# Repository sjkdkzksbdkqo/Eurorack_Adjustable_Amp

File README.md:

# Eurorack_Adjustable_Amp
2HP TL072-based 1 Channel Non-Inverting Amp with adjustable gain and Offset.

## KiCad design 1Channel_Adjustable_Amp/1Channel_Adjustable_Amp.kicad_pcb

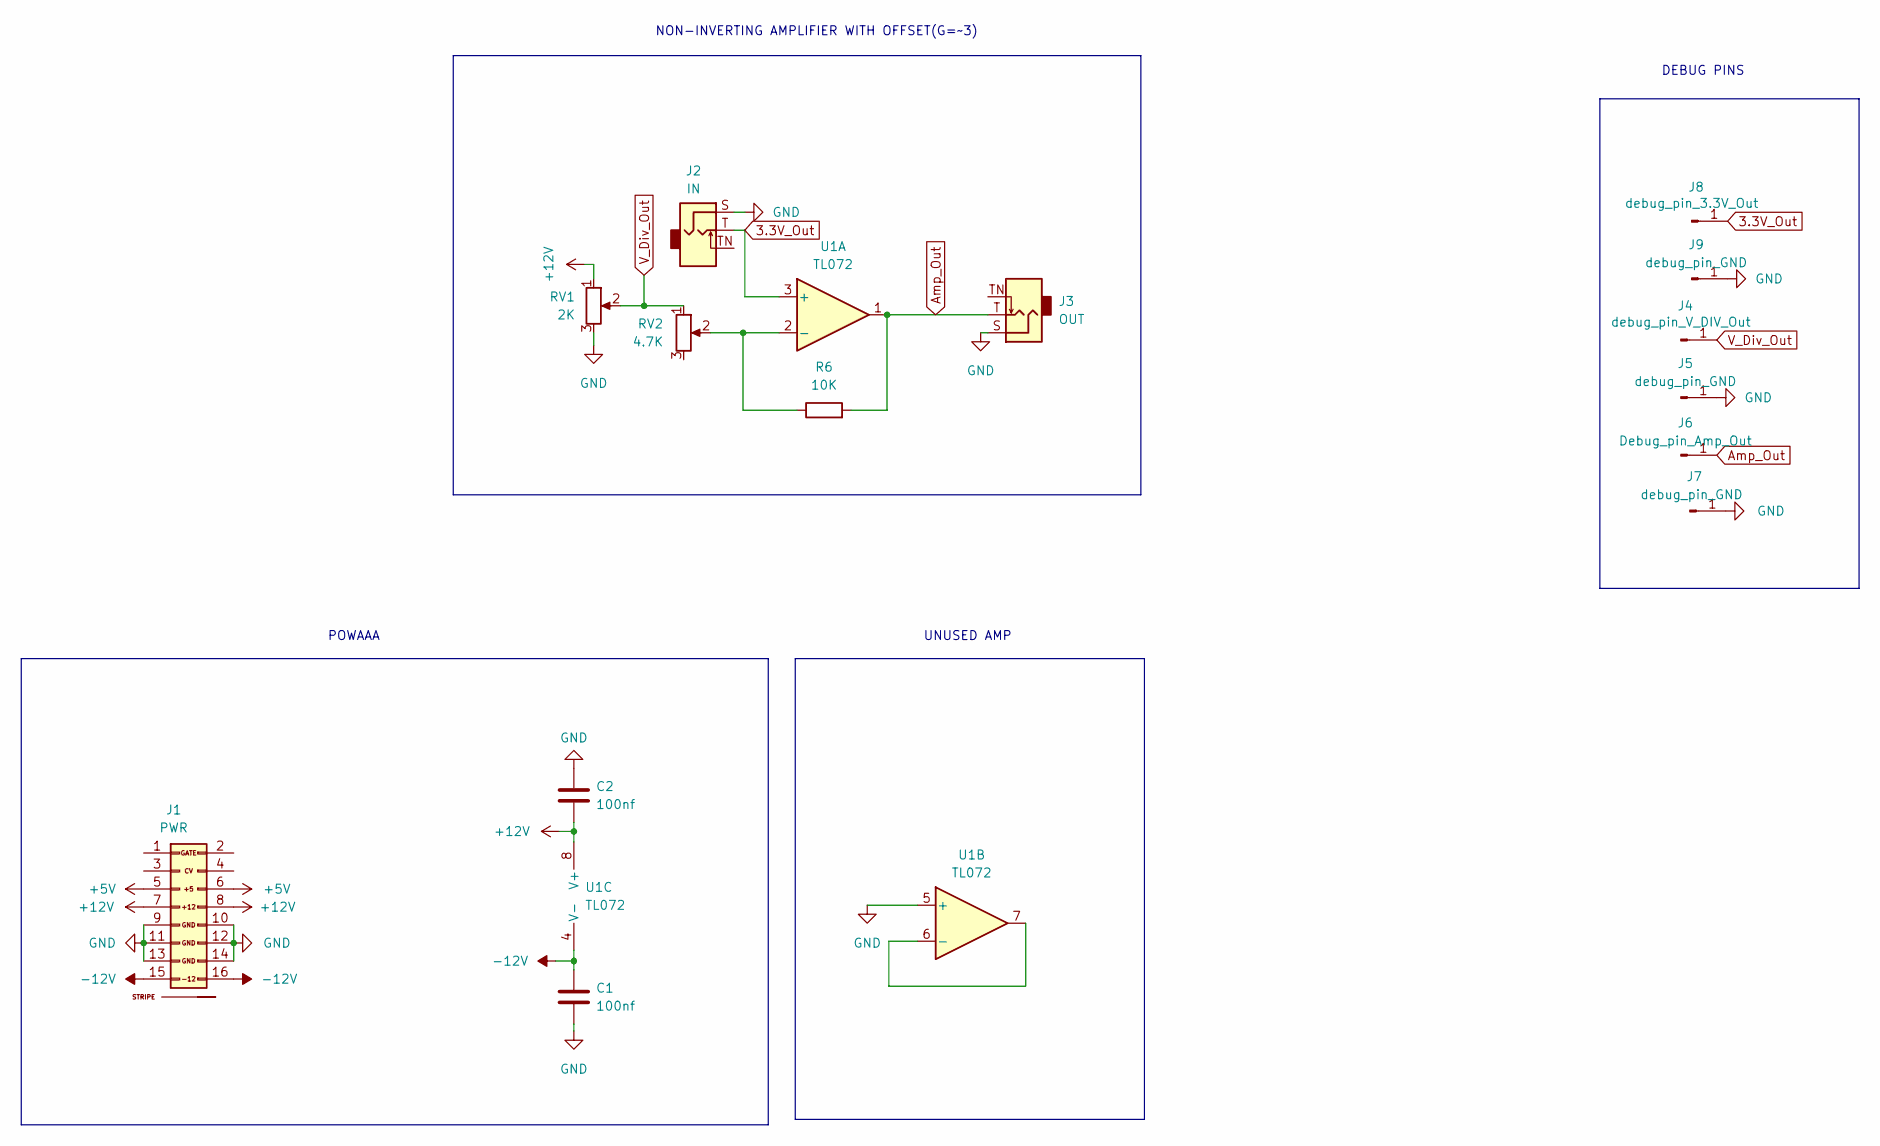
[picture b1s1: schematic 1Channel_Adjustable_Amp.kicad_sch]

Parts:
C1, C2: 100nf; C_0402_1005Metric_Pad0.74x0.62mm_HandSolder
J1: PWR; Pins_2x08_2.54mm_TH_EuroPower_Shrouded; Part Number LL1007-1 (2*8 HITEMP)
J2: IN; Jack_3.5mm_QingPu_WQP-PJ398SM_Vertical_CircularHoles
J3: OUT; Jack_3.5mm_QingPu_WQP-PJ398SM_Vertical_CircularHoles
J4: debug_pin_V_DIV_Out; TestPoint_Pad_D1.5mm
J5, J7, J9: debug_pin_GND; TestPoint_Pad_1.0x1.0mm
J6: Debug_pin_Amp_Out; TestPoint_Pad_D1.5mm
J8: debug_pin_3.3V_Out; TestPoint_Pad_D1.5mm
R6: 10K; R_Axial_DIN0207_L6.3mm_D2.5mm_P7.62mm_Horizontal
RV1: 2K; Potentiometer_Runtron_RM-065_Vertical
RV2: 4.7K; Potentiometer_Runtron_RM-065_Vertical
U1: TL072; SOIC-8_3.9x4.9mm_Pitch1.27mm

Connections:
3.3V_Out: J2.T, J8.1, U1.3 (+)
+5V: J1.5 (+12V), J1.6
+12V: C2.2, J1.7 (12V), J1.8 (+12V), RV1.1, U1.8 (V+)
-12V: C1.1, J1.15 (-12V), J1.16, U1.4 (V-)
Amp_Out: J3.T, J6.1, R6.2, U1.1
GND: C1.2, C2.1, J1.9 (GND), J1.10 (GND), J1.11 (GND), J1.12 (GND), J1.13 (-12), J1.14 (-12V), J2.S, J3.S, J5.1, J7.1, J9.1, RV1.3, U1.5 (+)
unnamed: R6.1, RV2.2, U1.2 (-)
unnamed: U1.6 (-), U1.7
V_Div_Out: J4.1, RV1.2, RV2.1

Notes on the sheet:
UNUSED AMP
POWAAA
DEBUG PINS
NON-INVERTING AMPLIFIER WITH OFFSET(G=~3)

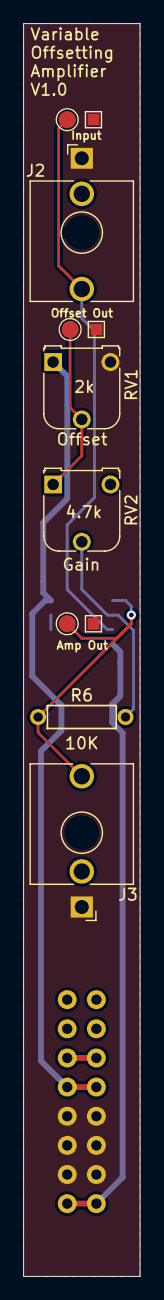
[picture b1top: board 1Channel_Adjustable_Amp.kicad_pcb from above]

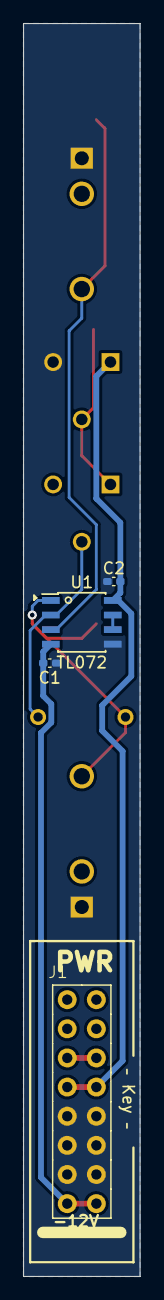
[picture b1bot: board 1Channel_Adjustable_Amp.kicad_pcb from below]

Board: 2 copper layers, 10.2 x 109.2 mm, 15 parts (4 on the bottom side), 9 nets.

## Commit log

2023-08-02 try no 1
    this is a test
2023-08-02 screenshot of 3d view
2023-08-02 board
